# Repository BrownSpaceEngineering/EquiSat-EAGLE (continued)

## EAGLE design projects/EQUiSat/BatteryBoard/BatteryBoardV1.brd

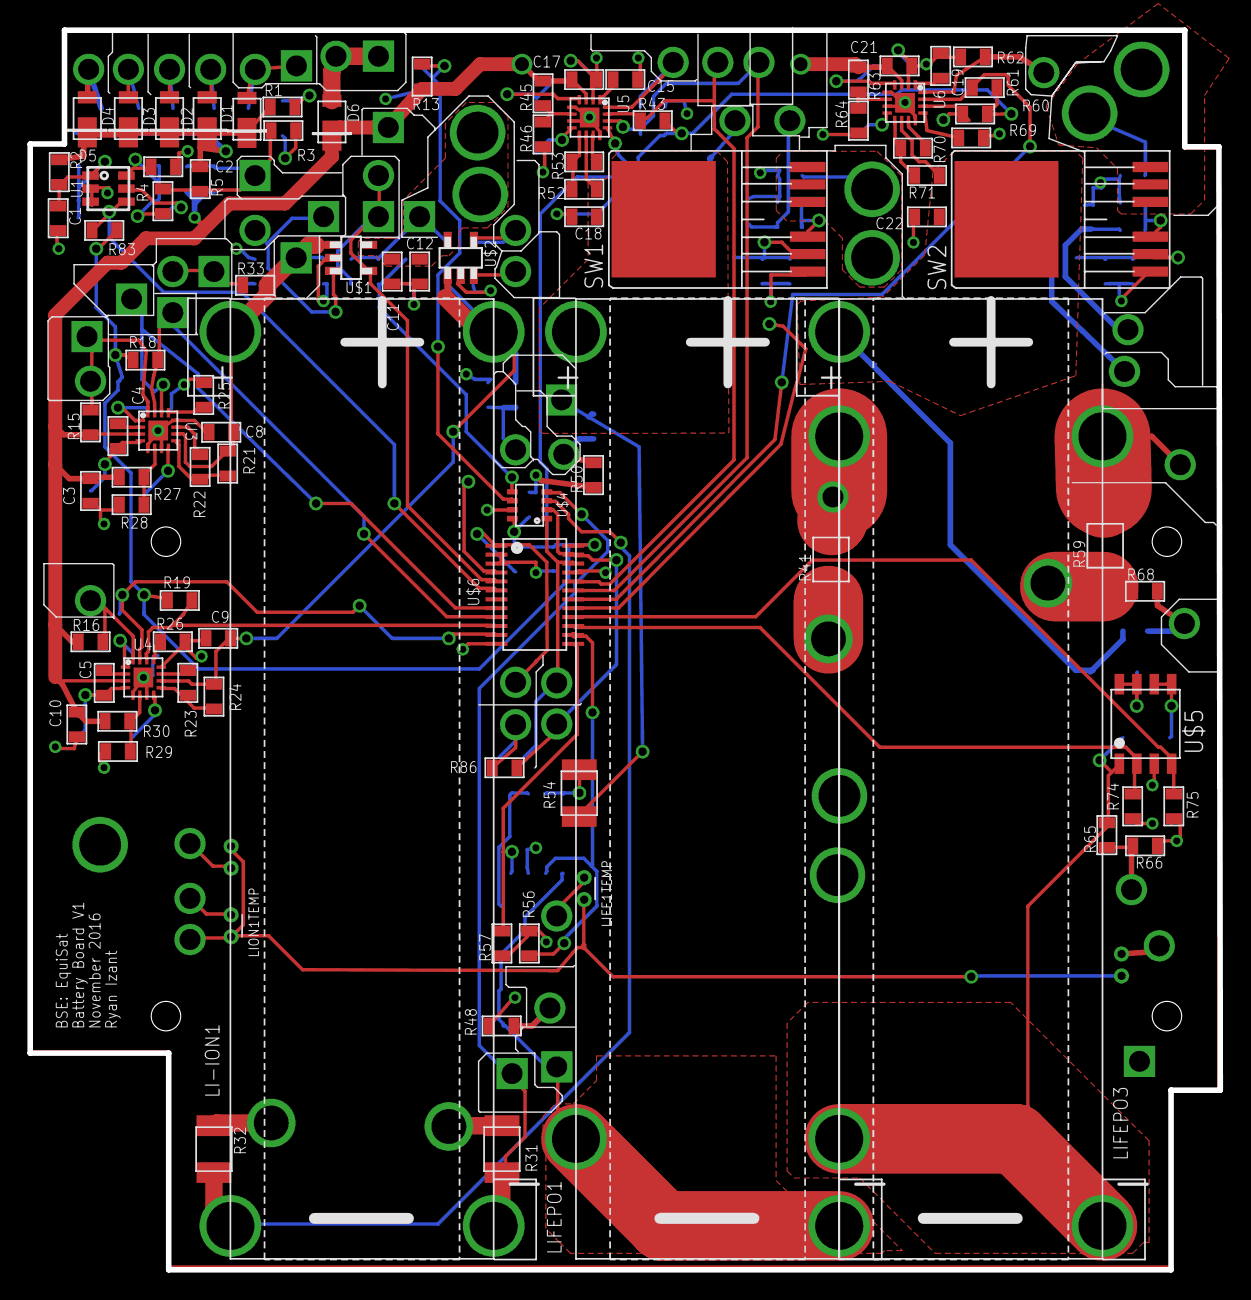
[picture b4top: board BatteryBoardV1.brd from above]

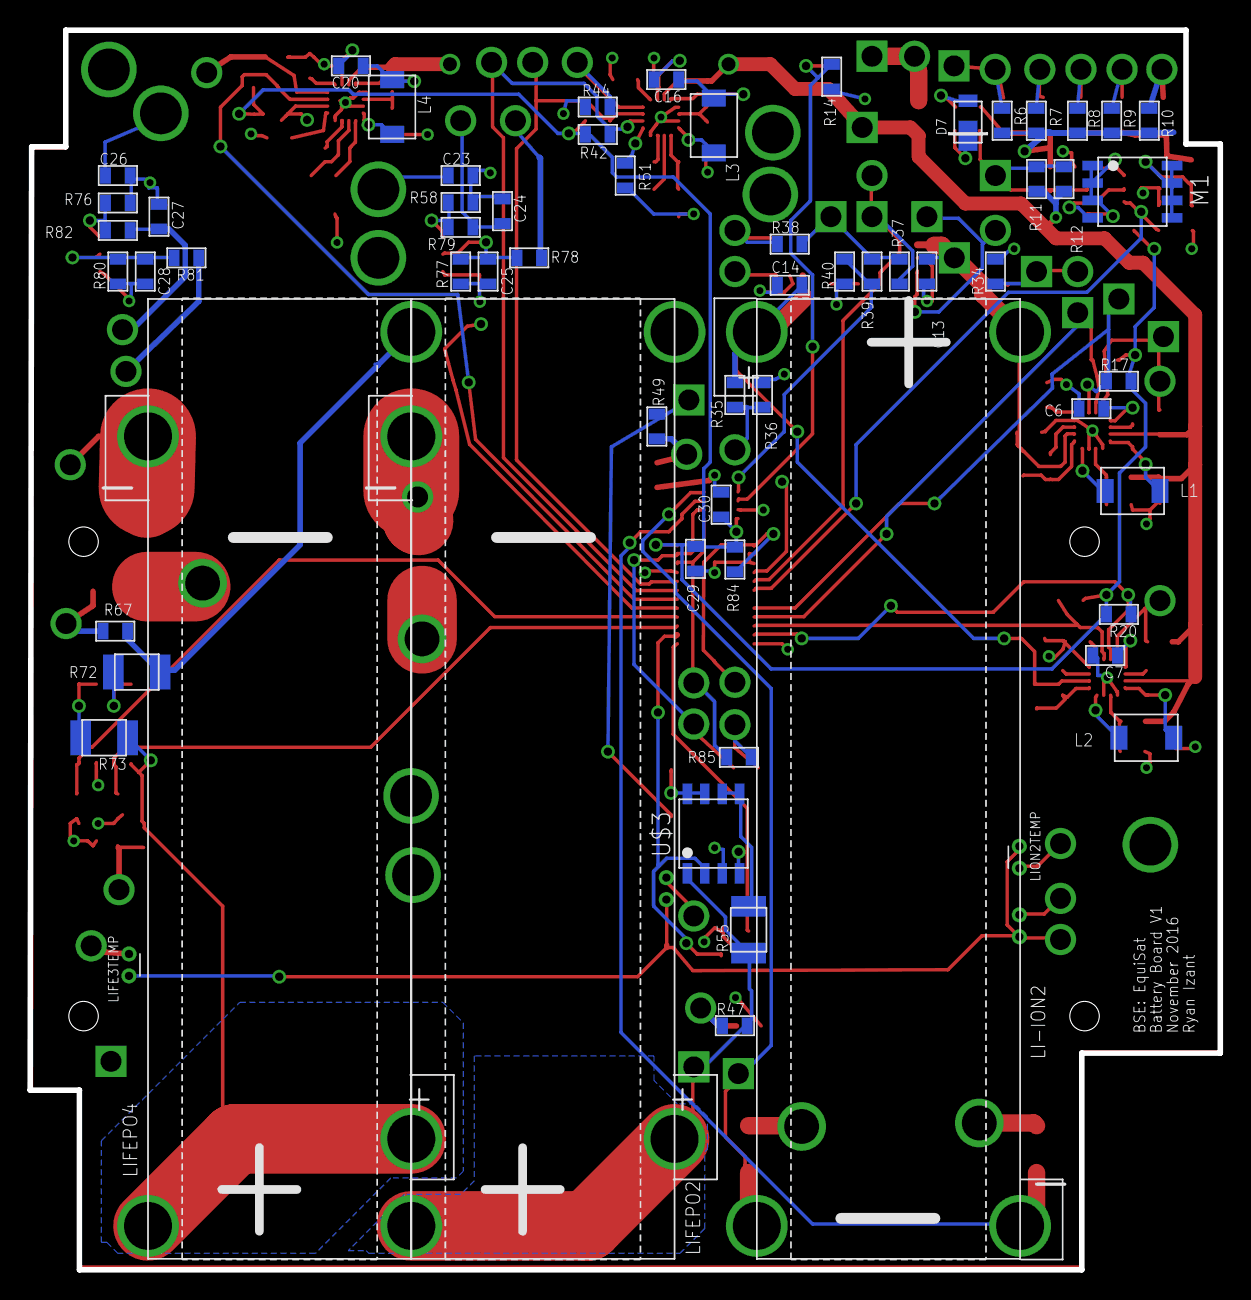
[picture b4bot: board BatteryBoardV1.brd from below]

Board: 4 copper layers, 86.8 x 90.4 mm, 213 parts (62 on the bottom side), 110 nets.

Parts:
C1, C2, C29, C30: 0.1uF; 0805
C3, C10, C17, C21: 10uF; 0805
C4, C5, C16, C20: 22nF; 0805
C6, C7, C15, C19: 2.2uF; 0805
C8, C9, C18, C22: 22uF; 0805
C11, C12: 4.7uF; 0805
C13, C14: 1uF; 0805
C23, C24, C26, C27: 10nF; 0805
C25, C28: 150nF; 0805
D1, D2, D3, D4, D5, D6, D7: DFLS130L; PWRDI-123
L1, L2, L3, L4: 120uH; 1812
LI-ION1, LI-ION2: ~4.1V; EQUISAT-BATTERY-VA
LIFE1TEMP, LIFE3TEMP: AD590FLATPACK; FLATPACK
LIFEPO1, LIFEPO3: ~3.5V; EQUISAT-BATTERY-VA
LIFEPO2, LIFEPO4: ~3.5V; EQUISAT-BATTERY-VB
LION1TEMP, LION2TEMP: AD590FLATPACK; FLATPACK
M1: BSO201SP; SO-8
R1, R2, R3, R4, R5, R6, R7, R8, R9, R10, R12: 0R; 0805
R11: 10R; 0805
R13: 40K; 0805
R14, R15, R16, R17, R18, R19, R20, R42, R43, R56, R57, R60, R61, R74, R75: 10K; 0805
R21, R24: 1M; 0805
R22, R23: 1.43M; 0805
R25, R26, R51, R69: 12.1K; 0805
R27, R30, R45, R63: 330K; 0805
R28, R29, R46, R64: 43K; 0805
R31, R32: 0.13R@1W; 1210
R33, R35, R39: 150K; 0805
R34, R36, R40, R44, R48, R50, R62, R66, R68: 100K; 0805
R37, R38, R83: 470K; 0805
R41, R59: 0.002R@1W; 1210
R47, R65: 95K; 0805
R49, R67: 287K; 0805
R52, R70: 887K; 0805
R53, R71: 1.74M; 0805
R54, R55, R72, R73: 34.8R@1W; 1210
R58, R76, R77, R80, R84: 1K; 0805
R78, R79, R81, R82: 4.7K; 0805
R85, R86: 2.4K; 0805
SW1, SW2: BTS50015-1TAD; TO-263-7-8
U1: LTC4412MPS6; TSOT23-6
U3, U4, U5, U6: LTC4121; QFN-16-PAD
U$1, U$2: LTC4411; TSOT23-5
U$3, U$5: VNS3NV04DP-E; SO-8
U$4: AD7991-0; SOT-23-8
U$6: TCA9535PWR; TSSOP-24
V1: UMB_CHG; VIA-60MIL
V2: X_P; VIA-60MIL
V3: X_N; VIA-60MIL
V4: Z_P; VIA-60MIL
V5: Z_N; VIA-60MIL
V6: Y_N; VIA-60MIL
V7: SP_C_O; VIA-60MIL-SQ
V8: SP_OUT; VIA-60MIL-SQ
V9: 5V; VIA-60MIL
V10: L1_CHG; VIA-60MIL
V11: !BATT_INT!; VIA-60MIL
V12: GND; VIA-60MIL-SQ
V13, V22, V23: GND; VIA-120MIL
V14: LIFEB1SNS; VIA-60MIL
V15: LF_B1_CHG; VIA-60MIL
V16: LIFE2; VIA-60MIL-SQ
V17: LIFE1; VIA-60MIL-SQ
V18: LF_B1_CHGN; VIA-60MIL
V19: LF_B1_FAULTN; VIA-60MIL
V20: LF_B1_OUTEN; VIA-60MIL
V21, V26: LF_B1; VIA-120MIL
V24: L1_TEMP; VIA-60MIL
V25: L1_REF; VIA-60MIL
V27, V28: LIFE_B2; VIA-120MIL
V29: L2_REF; VIA-60MIL
V30, V54: L_OUT; VIA-120MIL
V31: LF_B1_OSNS; VIA-60MIL
V32: L2_TEMP; VIA-60MIL
V33: L2_CHG; VIA-60MIL
V34: L1_DISG; VIA-60MIL
V35: L2_DISG; VIA-60MIL
V36: L1_ST; VIA-60MIL
V37: LF1_TEMP; VIA-60MIL
V38: L2_ST; VIA-60MIL
V39: UMB_CHG; VIA-60MIL-SQ
V40: L1_CHG; VIA-60MIL-SQ
V41: L1_FAULTN; VIA-60MIL-SQ
V42: L1_CHGN; VIA-60MIL-SQ
V43: L1_SNS; VIA-60MIL-SQ
V44: L1_REF; VIA-60MIL-SQ
V45: LION1; VIA-60MIL-SQ
V46: L1_DISG; VIA-60MIL-SQ
V47: L1_ST; VIA-60MIL-SQ
V48: L_OUT; VIA-60MIL-SQ
V49: X_P; VIA-60MIL-SQ
V50: LF3_TEMP; VIA-60MIL
V51: 3V3; VIA-60MIL
V52: SCL; VIA-60MIL
V53: SDA; VIA-60MIL
V56: LF_B2_OUTEN; VIA-60MIL
V57: LF_B2_CHG; VIA-60MIL
V58: LF1_REF; VIA-60MIL
V59: LF2_REF; VIA-60MIL
V60: LF_B2_SNS; VIA-60MIL
V61: LF4_REF; VIA-60MIL
V62: LF3_REF; VIA-60MIL
V63: LF_B2_OSNS; VIA-60MIL

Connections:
3V3: C29.1, C30.1, R17.2, R18.2, R19.2, R20.2, R42.2, R43.2, R60.2, R61.2, R83.2, R84.2, R85.2, R86.2, U$4.P$8, U$6.P$24, V51.P$1
5V: LIFE1TEMP.+, LIFE3TEMP.+, LION1TEMP.+, LION2TEMP.+, V9.P$1
!BATT_INT!: R84.1, U$6.P$1, V11.P$1
GND: C1.2, C2.2, C3.2, C6.2, C7.2, C8.2, C9.2, C10.2, C11.2, C12.2, C13.1, C14.1, C15.1, C17.1, C18.2, C19.1, C21.1, C22.2, C23.2, C24.2, C25.1, C26.2, C27.2, C28.1, C29.2, C30.2, R14.1, R25.1, R26.1, R28.1, R29.1, R31.P$1, R32.P$1, R34.1, R36.1, R40.1, R41.P$1, R44.1, R46.1, R48.1, R50.1, R51.2, R56.1, R57.1, R58.1, R59.P$1, R62.1, R64.1, R66.1, R68.1, R69.2, R74.1, R75.1, R76.1, R77.1, R80.1, SW1.P$1, SW2.P$1, U1.P$2, U1.P$3, U3.P$5, U3.P$7, U3.P$12, U3.P$17, U4.P$5, U4.P$7, U4.P$12, U4.P$17, U5.P$5, U5.P$7, U5.P$12, U5.P$17, U6.P$5, U6.P$7, U6.P$12, U6.P$17, U$1.P$2, U$2.P$2, U$3.P$3, U$4.P$7, U$5.P$3, U$6.P$2, U$6.P$3, U$6.P$12, U$6.P$21, V12.P$1, V13.P$1, V22.P$1, V23.P$1
L1_CHG: R15.2, U3.P$16, V10.P$1, V40.P$1
L1_CHGN: R17.1, U3.P$14, U$6.P$8, V42.P$1
L1_DISG: U$1.P$3, V34.P$1, V46.P$1
L1_FAULTN: R18.1, U3.P$15, U$6.P$9, V41.P$1
L1_REF: R33.1, R34.2, V25.P$1, V44.P$1
L1_SNS: LI-ION1.MINUS, R31.P$2, U$4.P$4, V43.P$1
L1_ST: R37.1, U$1.P$4, U$6.P$5, V36.P$1, V47.P$1
L1_TEMP: LION1TEMP.-, V24.P$1
L2_CHG: R16.2, U4.P$16, V33.P$1
L2_CHGN: R19.1, U4.P$14, U$6.P$10
L2_DISG: U$2.P$3, V35.P$1
L2_FAULTN: R20.1, U4.P$15, U$6.P$11
L2_REF: R35.1, R36.2, V29.P$1
L2_SNS: LI-ION2.MINUS, R32.P$2, U$4.P$3
L2_ST: R38.1, U$2.P$4, U$6.P$4, V38.P$1
L2_TEMP: LION2TEMP.-, V32.P$1
LF1_REF: R49.2, R50.2, V58.P$1
LF1_TEMP: LIFE1TEMP.-, V37.P$1
LF2_REF: R47.1, R48.2, V59.P$1
LF3_REF: R67.2, R68.2, V62.P$1
LF3_TEMP: LIFE3TEMP.-, V50.P$1
LF4_REF: R65.1, R66.2, V61.P$1
LF_B1: C23.1, SW1.P$5, SW1.P$6, SW1.P$7, V21.P$1, V26.P$1
LF_B1_BT: R57.2, U$3.P$4, U$6.P$13
LF_B1_CHG: R44.2, U5.P$16, V15.P$1
LF_B1_CHGN: R42.1, U5.P$14, U$6.P$19, V18.P$1
LF_B1_FAULTN: R43.1, U5.P$15, U$6.P$20, V19.P$1
LF_B1_OSNS: C24.1, R79.1, V31.P$1
LF_B1_OUTEN: R78.1, V20.P$1
LF_B1_TT: R56.2, U$3.P$2, U$6.P$14
LF_B2_BT: R75.2, U$5.P$4, U$6.P$16
LF_B2_CHG: R62.2, U6.P$16, V57.P$1
LF_B2_CHGN: R60.1, U6.P$14, U$6.P$17
LF_B2_FAULTN: R61.1, U6.P$15, U$6.P$18
LF_B2_OSNS: C27.1, R82.1, V63.P$1
LF_B2_OUTEN: R81.1, V56.P$1
LF_B2_SNS: LIFEPO4.MINUS, R59.P$2, V60.P$1
LF_B2_TT: R74.2, U$5.P$2, U$6.P$15
LIFE1: C18.1, LIFEPO1.PLUS, R49.1, R53.2, R54.P$2, SW1.PAD, U5.P$9, V17.P$1
LIFE2: LIFEPO1.MINUS, LIFEPO2.PLUS, R47.2, R55.P$1, U$3.P$1, V16.P$1
LIFE3: C22.1, LIFEPO3.PLUS, R67.1, R71.2, R72.P$2, SW2.PAD, U6.P$9
LIFE4: LIFEPO3.MINUS, LIFEPO4.PLUS, R65.2, R73.P$1, U$5.P$1
LIFEB1SNS: LIFEPO2.MINUS, R41.P$2, V14.P$1
LIFE_B2: C26.1, SW2.P$5, SW2.P$6, SW2.P$7, V27.P$1, V28.P$1
LION1: C8.1, C13.2, LI-ION1.PLUS, R21.2, R33.2, U3.P$9, U$1.P$1, V45.P$1
LION2: C9.1, C14.2, LI-ION2.PLUS, R24.2, R35.2, U4.P$9, U$2.P$1
L_OUT: C11.1, C12.1, R37.2, R38.2, R39.2, U$1.P$5, U$2.P$5, V30.P$1, V48.P$1, V54.P$1
L_REF: R39.1, R40.2, U$4.P$5
unnamed: M1.P$4, U1.P$5
unnamed: C2.1, M1.P$1, M1.P$2, M1.P$3, R4.1, U1.P$6
unnamed: D7.A, R1.2
unnamed: D7.C, R3.1
unnamed: C1.1, M1.P$5, M1.P$6, M1.P$7, M1.P$8, R2.2, U1.P$1
unnamed: R51.1, U5.P$13
unnamed: C4.2, L1.P$1, U3.P$4
unnamed: C4.1, U3.P$2
unnamed: C5.1, U4.P$2
unnamed: C5.2, L2.P$1, U4.P$4
unnamed: C7.1, U4.P$1
unnamed: C6.1, U3.P$1
unnamed: R23.1, U4.P$11
unnamed: R23.2, R24.1, U4.P$10
unnamed: R22.1, U3.P$11
unnamed: R21.1, R22.2, U3.P$10
unnamed: L1.P$2, U3.P$8
unnamed: R25.2, U3.P$13
unnamed: R26.2, U4.P$13
unnamed: R29.2, R30.1, U4.P$6
unnamed: R27.1, R28.2, U3.P$6
unnamed: L2.P$2, U4.P$8
unnamed: R54.P$1, U$3.P$7, U$3.P$8
unnamed: R55.P$2, U$3.P$5, U$3.P$6
unnamed: R52.1, U5.P$11
unnamed: R45.1, R46.2, U5.P$6
unnamed: R52.2, R53.1, U5.P$10
unnamed: C15.2, U5.P$1
unnamed: C16.1, L3.P$2, U5.P$4
unnamed: C16.2, U5.P$2
unnamed: L3.P$1, U5.P$8
unnamed: R63.1, R64.2, U6.P$6
unnamed: R69.1, U6.P$13
unnamed: R70.1, U6.P$11
unnamed: R70.2, R71.1, U6.P$10
unnamed: C19.2, U6.P$1
unnamed: C20.1, L4.P$2, U6.P$4
unnamed: C20.2, U6.P$2
unnamed: L4.P$1, U6.P$8
unnamed: R72.P$1, U$5.P$7, U$5.P$8
unnamed: R73.P$2, U$5.P$5, U$5.P$6
unnamed: C25.2, R77.2, R78.2, SW1.P$2
unnamed: R76.2, R82.2, SW2.P$3
unnamed: R58.2, R79.2, SW1.P$3
unnamed: C28.2, R80.2, R81.2, SW2.P$2
PANELREF: R13.1, R14.2, U$4.P$6
SCL: R85.1, U$4.P$1, U$6.P$22, V52.P$1
SDA: R86.1, U$4.P$2, U$6.P$23, V53.P$1
SPF_ST: R83.1, U1.P$4, U$6.P$6
SP_C: D1.C, D2.C, D3.C, D4.C, D5.C, R1.1, R2.1, R5.1, R6.2, R7.2, R8.2, R9.2, R10.2
SP_C_O: R3.2, R4.2, R5.2, R11.1, R12.1, V7.P$1
SP_OUT: C3.1, C10.1, C17.2, C21.2, D6.C, R11.2, R12.2, R13.2, R15.1, R16.1, R27.2, R30.2, R45.2, R63.2, U3.P$3, U4.P$3, U5.P$3, U6.P$3, V8.P$1
UMB_CHG: D6.A, V1.P$1, V39.P$1
X_N: D2.A, R7.1, V3.P$1
X_P: D1.A, R6.1, V2.P$1, V49.P$1
Y_N: D5.A, R10.1, V6.P$1
Z_N: D4.A, R9.1, V5.P$1
Z_P: D3.A, R8.1, V4.P$1

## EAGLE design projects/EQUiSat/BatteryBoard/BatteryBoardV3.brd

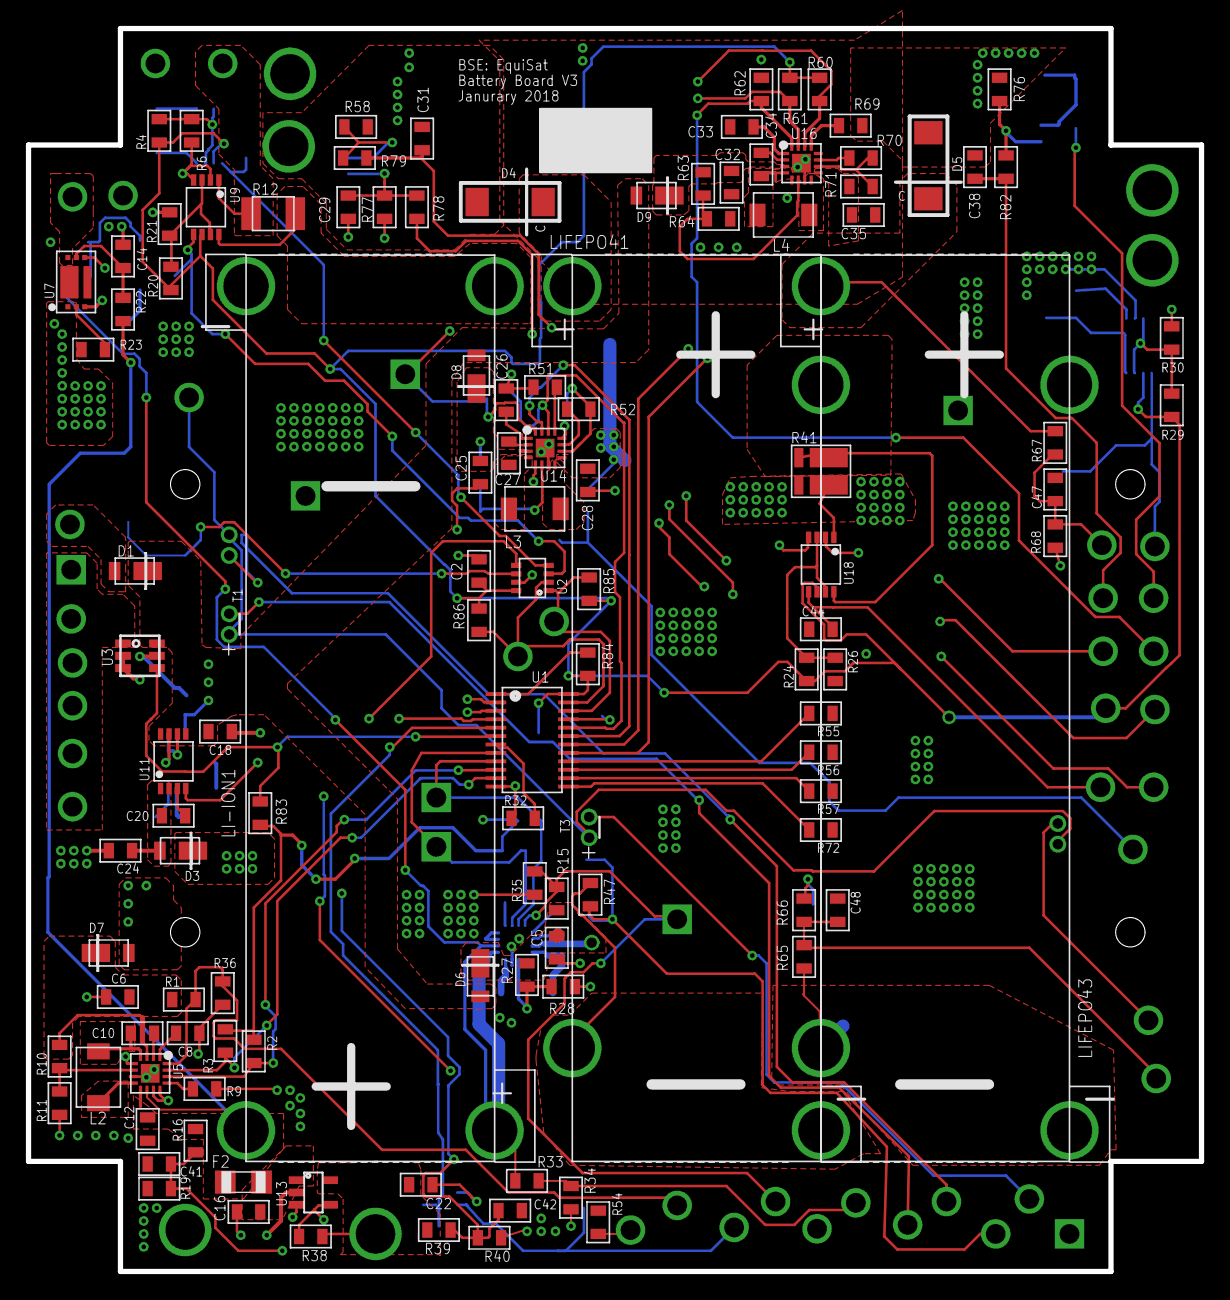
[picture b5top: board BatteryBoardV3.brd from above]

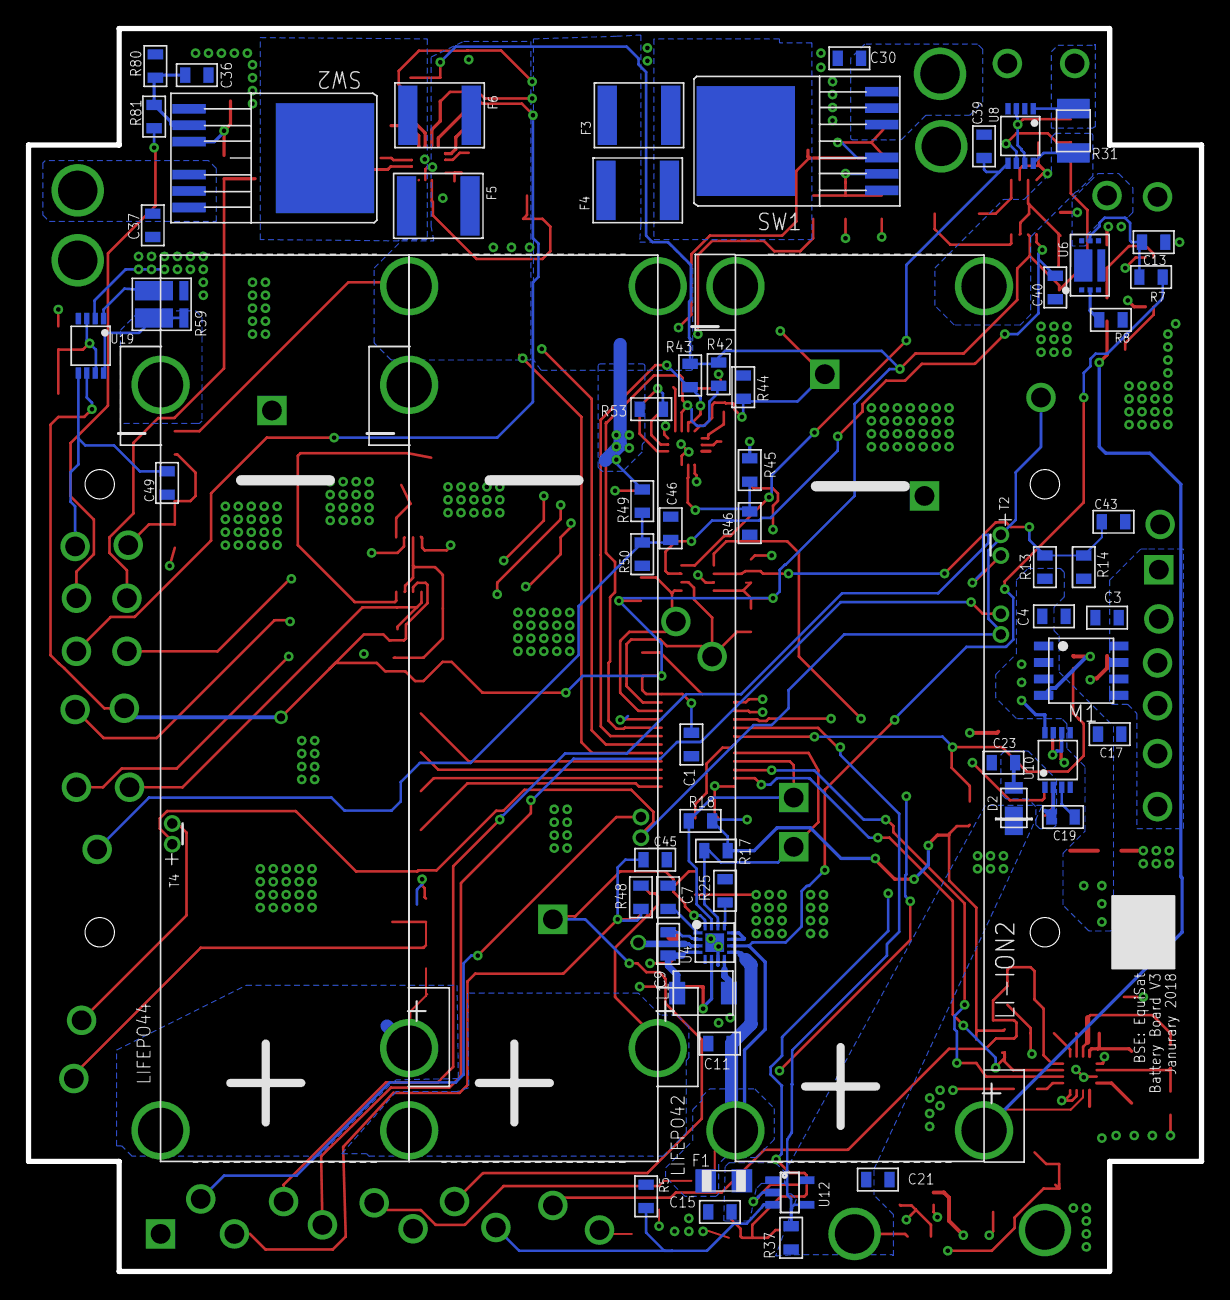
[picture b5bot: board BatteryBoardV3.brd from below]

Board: 4 copper layers, 90.6 x 96.0 mm, 235 parts (64 on the bottom side), 121 nets.

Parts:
C1, C2, C3, C4, C13, C14, C31, C38, C44, C49: 0.1uF; 0805
C5, C6, C23, C24, C25, C32: 10uF; 0805
C7, C8, C26, C33: 2.2uF; 0805
C9, C10, C27, C34: 22nF; 0805
C11, C12, C28, C35: 22uF; 0805
C15, C16, C17, C18, C39, C40, C41, C42, C43, C45, C46, C47, C48: 1uF; 0805
C19, C20: 0.01uF; 0805
C21, C22: 4.7uF; 0805
C29, C36: 150nF; 0805
C30, C37: 10nF; 0805
D1, D2, D3, D6, D7, D8, D9: DFLS130L; PWRDI-123
D4, D5: SMBJ5343B; DO214AA
F1, F2: 1206L200; 1206
F3, F4, F5, F6: 2016L500; 2016
L1, L2, L3, L4: 56uH; 1812
LI-ION1, LI-ION2: ~4.1V; EQUISAT-BATTERY-VA
LIFEPO41, LIFEPO43: ~3.5V; EQUISAT-BATTERY-VA
LIFEPO42, LIFEPO44: ~3.5V; EQUISAT-BATTERY-VB
M1: BSO201SP; SO-8
MTG1, MTG2, MTG3, MTG4: #2-CLOSE-NPTH
R1, R15: 40.9K; 0805
R2, R3, R17, R18, R37, R38, R42, R43, R60, R61, R83: 470K; 0805
R4, R20, R24, R29: 220K; 0805
R5, R6, R19, R21, R26, R30, R32, R34, R35, R36, R44, R48, R50, R54, R55, R56, R57, R62, R66, R68, R72, R77, R80: 100K; 0805
R7, R22: 680R; 0805
R8, R23, R58, R76: 1K; 0805
R9, R25, R51, R69: 6.04K; 0805
R10, R27, R45, R63: 330K; 0805
R11, R28, R46, R64: 43K; 0805
R12, R31: 0.025R@1W; 1210
R13: 40K; 0805
R14, R40: 10K; 0805
R16, R33: 150K; 0805
R39: 15K; 0805
R41, R59: 0.001R@3W; 1216
R47, R65: 95K; 0805
R49, R67: 287K; 0805
R52, R70: 887K; 0805
R53, R71: 1.74M; 0805
R78, R79, R81, R82: 4.7K; 0805
R84: 1M; 0805
R85, R86: 2.4K; 0805
SW1, SW2: BTS50015-1TAD; TO-263-7-8
T1, T2, T3, T4: AD590FLATPACK; FLATPACK
U1: TCA9535PWR; TSSOP-24
U2: AD7991-0; SOT-23-8
U3: LTC4412MPS6; TSOT23-6
U4, U5: LTC4121-4.2; QFN-16-PAD
U6, U7: LC05111C13MTTTG; WDFN6
U8, U9, U18, U19: AD8418; MSOP-8
U10, U11: LT1962-3; MSOP-8
U12, U13: LTC4411; TSOT23-5
U14, U16: LTC4121; QFN-16-PAD
V1, V2, V4: GND; VIA-120MIL
V3, V28, V36: GND; VIA-60MIL-SQ
V5: SCL; VIA-60MIL
V6: SDA; VIA-60MIL
V7: 5V; VIA-60MIL
V8: L1_TEMP; VIA-60MIL
V9: L2_TEMP; VIA-60MIL
V10: LF1_TEMP; VIA-60MIL
V11: LF3_TEMP; VIA-60MIL
V12: 3V3; VIA-60MIL
V13: X_P; VIA-60MIL
V14: X_P; VIA-60MIL-SQ
V15: X_N; VIA-60MIL
V16: Z_P; VIA-60MIL
V17: Z_N; VIA-60MIL
V18: Y_N; VIA-60MIL
V19: UMB_CHG; VIA-60MIL
V20: L1_CHG; VIA-60MIL
V21: L1_REF; VIA-60MIL
V22: L1_GND+; VIA-60MIL
V23: L1_GND-; VIA-60MIL
V24: L2_GND+; VIA-60MIL
V25: L2_GND-; VIA-60MIL
V26: L1_FAULTN; VIA-60MIL-SQ
V27: L1_CHGN; VIA-60MIL-SQ
V29: L1_DISG; VIA-60MIL
V30: L2_DISG; VIA-60MIL
V31: L2_REF; VIA-60MIL
V32: LFB1_CHG; VIA-60MIL-SQ
V33: L2_CHG; VIA-60MIL
V34: L_OUT; VIA-120MIL
V35: LFB1_CHG; VIA-60MIL
V40: LFB1SNS; VIA-60MIL
V41: LF1_REF; VIA-60MIL
V42: LF2_REF; VIA-60MIL
V43: LFB1_OUTEN; VIA-60MIL
V44: LFB2SNS; VIA-60MIL
V45: LF_B1; VIA-120MIL
V46: LFB1_OSNS; VIA-60MIL
V47: LFB2_CHG; VIA-60MIL
V48: L1_CHG; VIA-60MIL-SQ
V49: LF3_REF; VIA-60MIL
V50: LF4_REF; VIA-60MIL
V51: LFB2_OUTEN; VIA-60MIL
V53: LF_B2; VIA-120MIL
V99: LFB2_OSNS; VIA-60MIL

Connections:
5V: T1.+, T2.+, T3.+, T4.+, V7.P$1
!BATT_INT!: R84.1, U1.P$1
+3V3: C1.1, C2.1, R2.2, R3.2, R4.1, R17.2, R18.2, R20.1, R24.1, R29.1, R42.2, R43.2, R60.2, R61.2, R83.2, R84.2, R85.2, R86.2, U1.P$24, U2.P$8, U8.P$6, U9.P$6, U18.P$6, U19.P$6, V12.P$1
GND: C1.2, C2.2, C3.2, C4.2, C5.2, C6.2, C7.2, C8.2, C11.2, C12.2, C13.1, C14.1, C15.1, C16.1, C17.2, C18.2, C21.2, C22.2, C23.2, C24.2, C25.1, C26.1, C28.2, C29.1, C30.2, C31.2, C32.1, C33.1, C35.2, C36.1, C37.2, C38.2, C39.1, C40.1, C41.2, C42.2, C43.2, C44.1, C45.1, C46.1, C47.1, C48.1, C49.1, D4.A, D5.A, R5.1, R6.2, R8.1, R9.1, R11.1, R14.1, R19.1, R21.2, R23.1, R25.1, R26.2, R28.1, R30.2, R32.1, R34.1, R35.1, R36.1, R40.1, R41.P$1, R41.P$2, R44.1, R46.1, R48.1, R50.1, R51.2, R54.1, R55.1, R56.1, R57.1, R58.1, R59.P$1, R59.P$2, R62.1, R64.1, R66.1, R68.1, R69.2, R72.1, R76.1, R77.1, R80.1, SW1.P$1, SW2.P$1, U1.P$2, U1.P$3, U1.P$12, U1.P$21, U2.P$7, U3.P$2, U3.P$3, U4.P$5, U4.P$7, U4.P$11, U4.P$12, U4.P$17, U5.P$5, U5.P$7, U5.P$11, U5.P$12, U5.P$17, U6.P$1, U6.P$3, U6.P$4, U7.P$1, U7.P$3, U7.P$4, U8.P$2, U8.P$4, U9.P$2, U9.P$4, U10.P$4, U10.P$6, U10.P$7, U11.P$4, U11.P$6, U11.P$7, U12.P$2, U13.P$2, U14.P$5, U14.P$7, U14.P$12, U14.P$17, U16.P$5, U16.P$7, U16.P$12, U16.P$17, U18.P$1, U18.P$2, U18.P$4, U19.P$1, U19.P$2, U19.P$4, V1.P$1, V2.P$1, V3.P$1, V4.P$1, V28.P$1, V36.P$1
L1_CHG: R15.2, R35.2, U4.P$16, V20.P$1, V48.P$1
L1_CHGN: R17.1, U1.P$8, U4.P$14, V27.P$1
L1_DISG: R5.2, U12.P$3, V29.P$1
L1_FAULTN: R18.1, U1.P$9, U4.P$15, V26.P$1
L1_PROG: R25.2, U4.P$13
L1_REF: R33.1, R34.2, V21.P$1
L1_SNS: C39.2, U2.P$4, U8.P$5
L1_SNS+: LI-ION1.MINUS, R31.P$2, U8.P$8
L1_SNS-: R31.P$1, U8.P$1, V22.P$1
L1_ST: R37.1, U1.P$5, U12.P$4
L1_TEMP: T1.-, V8.P$1
L2_CHG: R1.2, R36.2, U5.P$16, V33.P$1
L2_CHGN: R2.1, U1.P$10, U5.P$14
L2_DISG: R54.2, U13.P$3, V30.P$1
L2_FAULTN: R3.1, U1.P$11, U5.P$15
L2_PROG: R9.2, U5.P$13
L2_REF: C41.1, R16.1, R19.2, V31.P$1
L2_SNS: C40.2, U2.P$3, U9.P$5
L2_SNS+: LI-ION2.MINUS, R12.P$2, U9.P$8
L2_SNS-: R12.P$1, U9.P$1, V24.P$1
L2_ST: R38.1, U1.P$4, U13.P$4
L2_TEMP: T2.-, V9.P$1
LF1_REF: C46.2, R49.2, R50.2, V41.P$1
LF1_TEMP: T3.-, V10.P$1
LF2_REF: C45.2, R47.1, R48.2, V42.P$1
LF3_REF: C47.2, R67.2, R68.2, V49.P$1
LF3_TEMP: T4.-, V11.P$1
LF4_REF: C48.2, R65.1, R66.2, V50.P$1
LF-B1-CHG-IN: C25.2, D8.C, R45.2, U14.P$3
LF-B2-CHG-IN: C32.2, D9.C, R63.2, U16.P$3
LFB1_SNS+: LIFEPO42.MINUS, R41.P$3, R41.P$4, U18.P$8
LFB2_SNS+: LIFEPO44.MINUS, R59.P$3, R59.P$4, U19.P$8
LF_B1: C30.1, SW1.P$5, SW1.P$6, SW1.P$7, V45.P$1
LF_B1_CHG: R44.2, U14.P$16, V32.P$1, V35.P$1
LF_B1_CHGN: R42.1, U1.P$20, U14.P$14
LF_B1_FAULTN: R43.1, U1.P$19, U14.P$15
LF_B1_OSNS: C31.1, R79.1, V46.P$1
LF_B1_OUTEN: R78.1, V43.P$1
LF_B1_SNS: C44.2, U18.P$5, V40.P$1
LF_B2: C37.1, SW2.P$5, SW2.P$6, SW2.P$7, V53.P$1
LF_B2_CHG: R62.2, U16.P$16, V47.P$1
LF_B2_CHGN: R60.1, U1.P$17, U16.P$14
LF_B2_FAULTN: R61.1, U1.P$18, U16.P$15
LF_B2_OSNS: C38.1, R82.1, V99.P$1
LF_B2_OUTEN: R81.1, V51.P$1
LF_B2_SNS: C49.2, U19.P$5, V44.P$1
LIFE1: C28.1, D4.C, F3.P$1, F4.P$1, LIFEPO41.PLUS, R49.1, R53.2, U14.P$9
LIFE1FUSEOUT: F3.P$2, F4.P$2, SW1.PAD
LIFE2: LIFEPO41.MINUS, LIFEPO42.PLUS, R47.2
LIFE3: C35.1, D5.C, F5.P$1, F6.P$1, LIFEPO43.PLUS, R67.1, R71.2, U16.P$9
LIFE3FUSEOUT: F5.P$2, F6.P$2, SW2.PAD
LIFE4: LIFEPO43.MINUS, LIFEPO44.PLUS, R65.2
LION1: C11.1, F1.1, LI-ION1.PLUS, R7.2, R33.2, U4.P$9, U4.P$10
LION1-CHG-IN: C5.1, D6.C, R15.1, R27.2, U4.P$3
LION1_OUT: C15.2, F1.2, U12.P$1
LION2: C12.1, F2.1, LI-ION2.PLUS, R16.2, R22.2, U5.P$9, U5.P$10
LION2-CHG-IN: C6.1, D7.C, R1.1, R10.2, U5.P$3
LION2_OUT: C16.2, F2.2, U13.P$1
L_OUT: C21.1, C22.1, D2.C, D3.C, R37.2, R38.2, R39.2, U12.P$5, U13.P$5, V34.P$1
L_REF: C42.1, R39.1, R40.2, U2.P$5
unnamed: M1.P$4, U3.P$5
unnamed: C20.1, C24.1, D3.A, U11.P$1, U11.P$2
unnamed: C19.1, C23.1, D2.A, U10.P$1, U10.P$2
unnamed: C20.2, U11.P$3
unnamed: C19.2, U10.P$3
unnamed: C10.2, L2.P$1, U5.P$4
unnamed: R51.1, U14.P$13
unnamed: C9.2, L1.P$1, U4.P$4
unnamed: C9.1, U4.P$2
unnamed: R29.2, R30.1, U19.P$3, U19.P$7
unnamed: R24.2, R26.1, U18.P$3, U18.P$7
unnamed: C7.1, U4.P$1
unnamed: C10.1, U5.P$2
unnamed: R32.2, U1.P$7
unnamed: U6.P$6, V23.P$1
unnamed: C8.1, U5.P$1
unnamed: L1.P$2, U4.P$8
unnamed: R72.2, U1.P$13
unnamed: R57.2, U1.P$14
unnamed: R27.1, R28.2, U4.P$6
unnamed: R56.2, U1.P$15
unnamed: R55.2, U1.P$16
unnamed: R52.1, U14.P$11
unnamed: R45.1, R46.2, U14.P$6
unnamed: R52.2, R53.1, U14.P$10
unnamed: C26.2, U14.P$1
unnamed: C27.1, L3.P$2, U14.P$4
unnamed: C27.2, U14.P$2
unnamed: L3.P$1, U14.P$8
unnamed: R63.1, R64.2, U16.P$6
unnamed: R4.2, R6.1, U8.P$3, U8.P$7
unnamed: R69.1, U16.P$13
unnamed: R70.1, U16.P$11
unnamed: R70.2, R71.1, U16.P$10
unnamed: C33.2, U16.P$1
unnamed: C34.1, L4.P$2, U16.P$4
unnamed: C34.2, U16.P$2
unnamed: L4.P$1, U16.P$8
unnamed: C13.2, R7.1, U6.P$5
unnamed: R8.2, U6.P$2
unnamed: R10.1, R11.2, U5.P$6
unnamed: L2.P$2, U5.P$8
unnamed: R20.2, R21.1, U9.P$3, U9.P$7
unnamed: U7.P$6, V25.P$1
unnamed: R23.2, U7.P$2
unnamed: C14.2, R22.1, U7.P$5
unnamed: C29.2, R77.2, R78.2, SW1.P$2
unnamed: R76.2, R82.2, SW2.P$3
unnamed: R58.2, R79.2, SW1.P$3
unnamed: C36.2, R80.2, R81.2, SW2.P$2
PANELREF: C43.1, R13.1, R14.2, U2.P$6
SCL: R85.1, U1.P$22, U2.P$1, V5.P$1
SDA: R86.1, U1.P$23, U2.P$2, V6.P$1
SPF_ST: R83.1, U1.P$6, U3.P$4
SP_C: C3.1, M1.P$5, M1.P$6, M1.P$7, M1.P$8, U3.P$1, V13.P$1, V14.P$1, V15.P$1, V16.P$1, V17.P$1, V18.P$1
SP_OUT: C4.1, C17.1, C18.1, D1.C, D6.A, D7.A, D8.A, D9.A, M1.P$1, M1.P$2, M1.P$3, R13.2, U3.P$6, U10.P$5, U10.P$8, U11.P$5, U11.P$8
UMB_CHG: D1.A, V19.P$1
